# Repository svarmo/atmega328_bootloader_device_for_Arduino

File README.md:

# Overview
The objective of this project is to create a fully functional Arduino Bootloader for the ATMega328 MCU.

This project will include all the sources to manufacture the programmer device, it includes the 3D printed model, the PCB manufacturing files as well as the source code for the device.

# License
This project is licenses under an MIT license, view attached file for more detail.

The MCU is works using Arduino and **HEAVILY** relies on code provided by Nick Gammon's Arduino_sketch code: https://github.com/nickgammon/arduino_sketches (Also MIT license)

All the hardware is designed by me and falls under **Open Hardware** spec so feel free to use, modify as you see fit.

## Special contributors
* Ricardo Rodriguez
* Nick Gammon

# Usage
TODO: Populate how to use

# Notes
At this point, a good write looks like this:

```
Started
Waiting 2 seconds
Attempting to enter ICSP programming mode ...ok

Getting signature
Processor = ATmega328P

*CURRENT FUSE VALUES*
Low_Fuse = E2
High_fuse = DA
Ext_Fuse = FD
Lock_Fuse = EF
Clock_Calibration_Fuse = 96

Using Lilypad 8 MHz loader.

Bootloader address = 7800
Bootloader length = 1932

*NEW FUSE VALUES*
Low_Fuse = E2
High_Fuse = DA
Ext_Fuse = 5
Lock_Fuse = 2F
Erasing chip ...
Writing bootloader ...
Written.
Verifying ...
No errors found.

Writing fuses ...

*CURRENT FUSE VALUES*
Low_Fuse = E2
High_fuse = DA
Ext_Fuse = FD
Lock_Fuse = EF
Clock_Calibration_Fuse = 96

Done.
Programming mode off.
```

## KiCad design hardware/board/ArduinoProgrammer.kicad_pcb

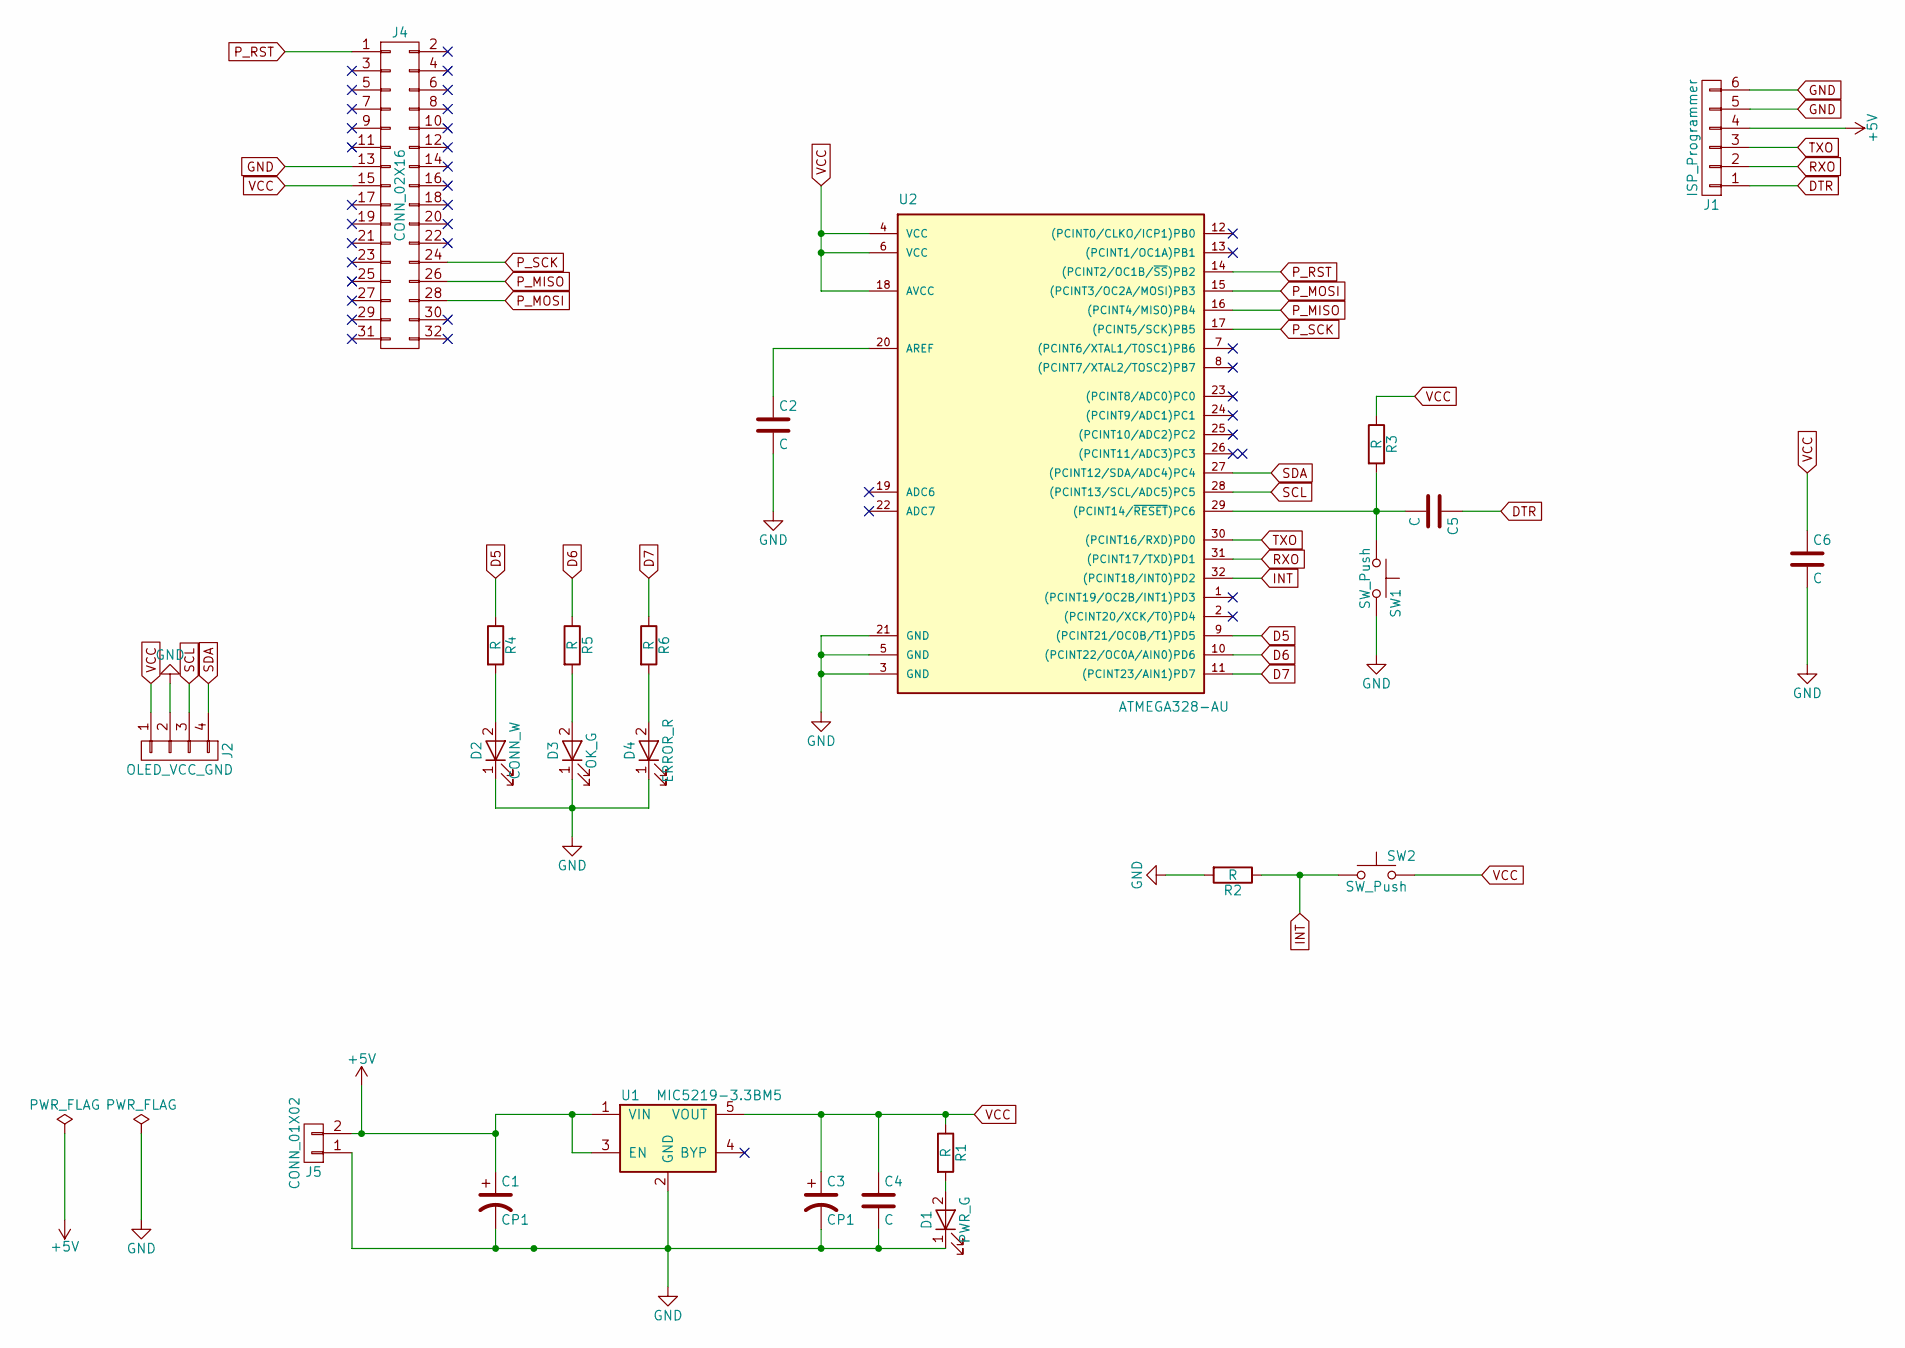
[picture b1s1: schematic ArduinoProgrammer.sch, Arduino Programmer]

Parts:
C1, C3: CP1; CP_Tantalum_Case-A_EIA-3216-18_Reflow
C2, C4, C5, C6: C; C_0805
D1: PWR_G; LED_0805
D2: CONN_W; LED_0805
D3: OK_G; LED_0805
D4: ERROR_R; LED_0805
J1: ISP_Programmer; Pin_Header_Straight_1x06_Pitch2.00mm
J2: OLED_VCC_GND
J4: CONN_02X16; ProgSocket
J5: CONN_01X02; Pin_Header_Straight_1x02_Pitch2.00mm
R1, R2, R3, R4, R5, R6: R; R_0805
SW1, SW2: SW_Push; SW_SPST_FSMSM
U1: MIC5219-3.3BM5; SOT-23-5
U2: ATMEGA328-AU; TQFP-32_7x7mm_Pitch0.8mm

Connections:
+5V: C1.1, J1.4, J5.2, U1.1 (VIN), U1.3 (EN)
D5: R4.1, U2.9 ((PCINT21/OC0B/T1)PD5)
D6: R5.1, U2.10 ((PCINT22/OC0A/AIN0)PD6)
D7: R6.1, U2.11 ((PCINT23/AIN1)PD7)
DTR: C5.1, J1.1
GND: C1.2, C2.2, C3.2, C4.2, C6.2, D1.1 (K), D2.1 (K), D3.1 (K), D4.1 (K), J1.5, J1.6, J2.2 (GND), J4.13, J5.1, R2.2, SW1.2, U1.2 (GND), U2.3 (GND), U2.5 (GND), U2.21 (GND)
INT: R2.1, SW2.1, U2.32 ((PCINT18/INT0)PD2)
unnamed: C2.1, U2.20 (AREF)
unnamed: C5.2, R3.2, SW1.1, U2.29 ((PCINT14/~RESET~)PC6)
unnamed: D1.2 (A), R1.2
unnamed: D2.2 (A), R4.2
unnamed: D3.2 (A), R5.2
unnamed: D4.2 (A), R6.2
P_MISO: J4.26, U2.16 ((PCINT4/MISO)PB4)
P_MOSI: J4.28, U2.15 ((PCINT3/OC2A/MOSI)PB3)
P_RST: J4.1, U2.14 ((PCINT2/OC1B/~SS~)PB2)
P_SCK: J4.24, U2.17 ((PCINT5/SCK)PB5)
RXO: J1.2, U2.31 ((PCINT17/TXD)PD1)
SCL: J2.3 (SCL), U2.28 ((PCINT13/SCL/ADC5)PC5)
SDA: J2.4 (SDA), U2.27 ((PCINT12/SDA/ADC4)PC4)
TXO: J1.3, U2.30 ((PCINT16/RXD)PD0)
VCC: C3.1, C4.1, C6.1, J2.1 (VCC), J4.15, R1.1, R3.1, SW2.2, U1.5 (VOUT), U2.4 (VCC), U2.6 (VCC), U2.18 (AVCC)

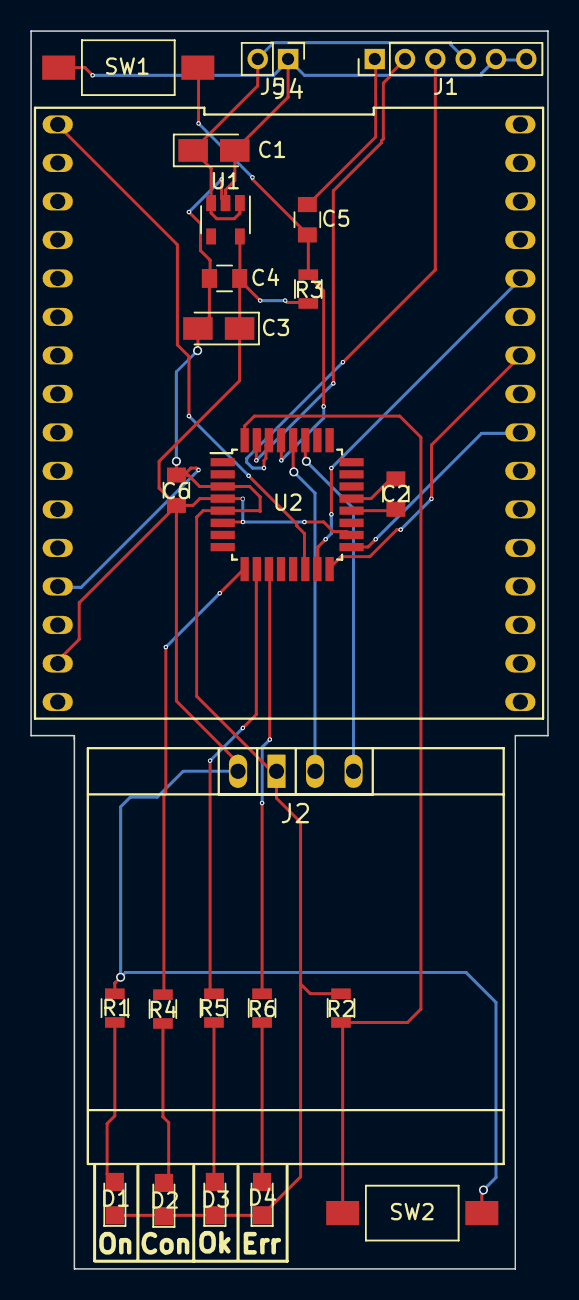
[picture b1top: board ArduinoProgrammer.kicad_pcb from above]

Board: 2 copper layers, 34.1 x 81.7 mm, 24 parts (0 on the bottom side), 22 nets.

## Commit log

2017-09-07 Added project skeleton
2017-09-07 Enabled all function up to writeBootloader
2017-09-07 All compiles
2017-09-07 Enabled write bootloader and fuses (Not actually writing)
2017-09-08 Writing booloader working
2017-09-09 Added ifdef tags
2017-09-09 Variable/Constants cleanup (Not working yet)
2017-09-09 First working version
    - Writes to AtMega328
    - All files clumped together
2017-09-09 Working bootloader upload
2017-09-14 Added address search
2017-09-14 Initial OLED implementation, Adafruit not working
2017-09-23 Screen working with the adafruit library
2017-10-03 Added schem
2017-10-05 Added pcb circuit with OSx auto-route
2018-02-22 Stash bootloader and screen intergation

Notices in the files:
hardware/board/ArduinoProgrammer.sch:
https://creativecommons.org/licenses/by-sa/4.0
Attribution-ShareAlike 4.0 International (CC BY-SA 4.0)
Released under Creative Commons
